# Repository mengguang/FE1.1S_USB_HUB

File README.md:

# FE1.1S_USB_HUB
USB Hub using FE1.1S chip.

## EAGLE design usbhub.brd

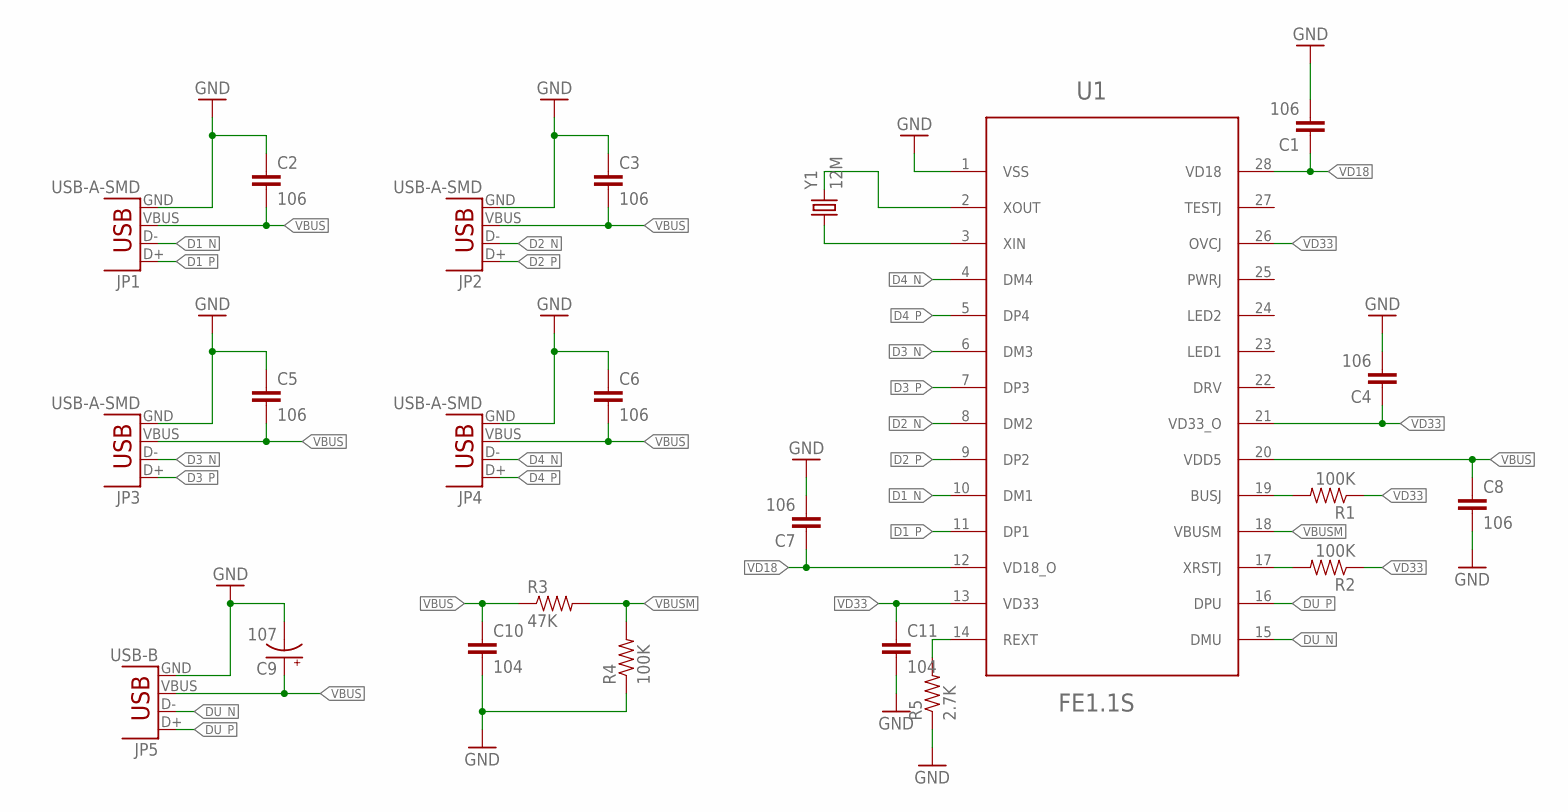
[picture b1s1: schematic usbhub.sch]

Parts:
C1, C2, C3, C4, C5, C6, C7, C8: 106; 0603-CAP
C9: 107; EIA3528-KIT
C10, C11: 104; 0603-CAP
JP1, JP2, JP3, JP4: USB-A-SMD; USB-A-S-NOSILK-FEMALE
JP5: USB-B; USB-B-PTH
R1, R2, R4: 100K; 0603-RES
R3: 47K; 0603-RES
R5: 2.7K; 0603-RES
U1: FE1.1S; SSOP28-39
Y1: 12M; HC49US

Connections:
D1_N: JP1.D-, U1.10 (DM1)
D1_P: JP1.D+, U1.11 (DP1)
D2_N: JP2.D-, U1.8 (DM2)
D2_P: JP2.D+, U1.9 (DP2)
D3_N: JP3.D-, U1.6 (DM3)
D3_P: JP3.D+, U1.7 (DP3)
D4_N: JP4.D-, U1.4 (DM4)
D4_P: JP4.D+, U1.5 (DP4)
DU_N: JP5.D-, U1.15 (DMU)
DU_P: JP5.D+, U1.16 (DPU)
GND: C1.2, C2.1, C3.1, C4.2, C5.1, C6.1, C7.2, C8.2, C9.C (-), C10.2, C11.2, JP1.GND, JP2.GND, JP3.GND, JP4.GND, JP5.GND, R4.1, R5.1, U1.1 (VSS)
unnamed: U1.2 (XOUT), Y1.2
unnamed: U1.3 (XIN), Y1.1
unnamed: R5.2, U1.14 (REXT)
unnamed: R1.2, U1.19 (BUSJ)
unnamed: R2.2, U1.17 (XRSTJ)
VBUS: C2.2, C3.2, C5.2, C6.2, C8.1, C9.A (+), C10.1, JP1.VBUS, JP2.VBUS, JP3.VBUS, JP4.VBUS, JP5.VBUS, R3.1, U1.20 (VDD5)
VBUSM: R3.2, R4.2, U1.18 (VBUSM)
VD18: C1.1, C7.1, U1.12 (VD18_O), U1.28 (VD18)
VD33: C4.1, C11.1, R1.1, R2.1, U1.13 (VD33), U1.21 (VD33_O), U1.26 (OVCJ)

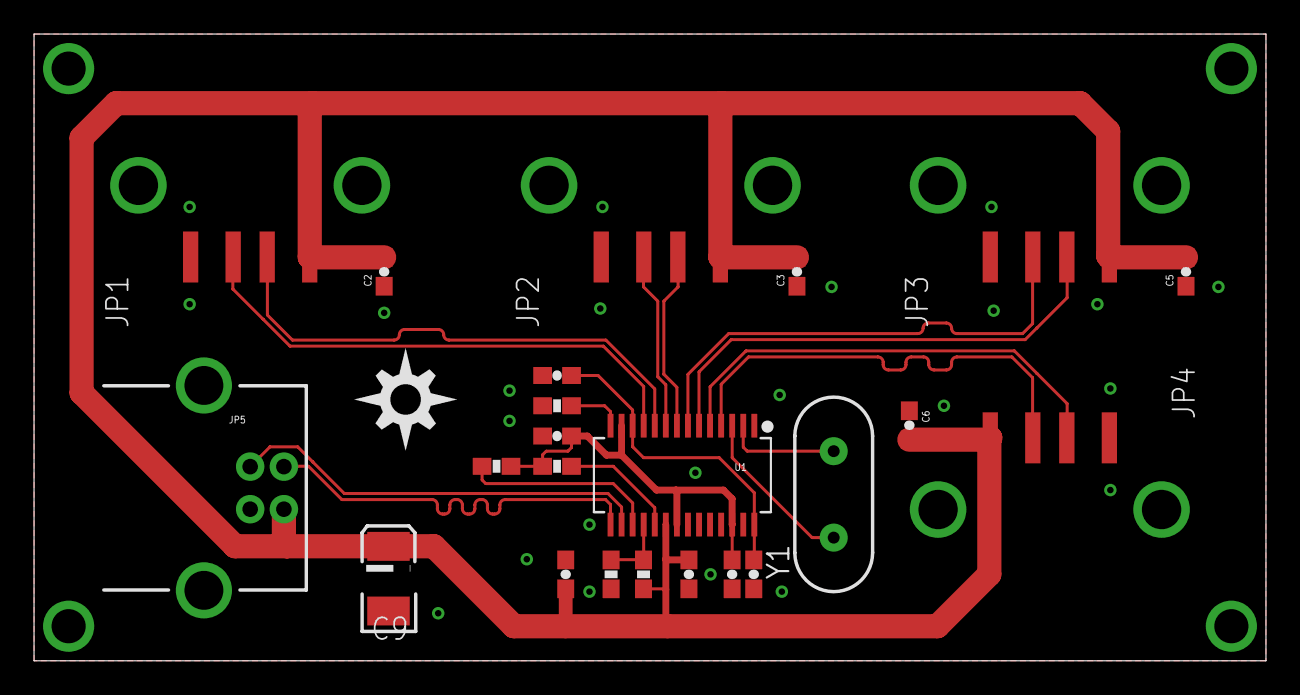
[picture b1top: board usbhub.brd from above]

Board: 2 copper layers, 72.4 x 36.8 mm, 24 parts (0 on the bottom side), 20 nets.

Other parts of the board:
U$1: DIYNOVA_LOGO

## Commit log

2017-10-31 version 3
